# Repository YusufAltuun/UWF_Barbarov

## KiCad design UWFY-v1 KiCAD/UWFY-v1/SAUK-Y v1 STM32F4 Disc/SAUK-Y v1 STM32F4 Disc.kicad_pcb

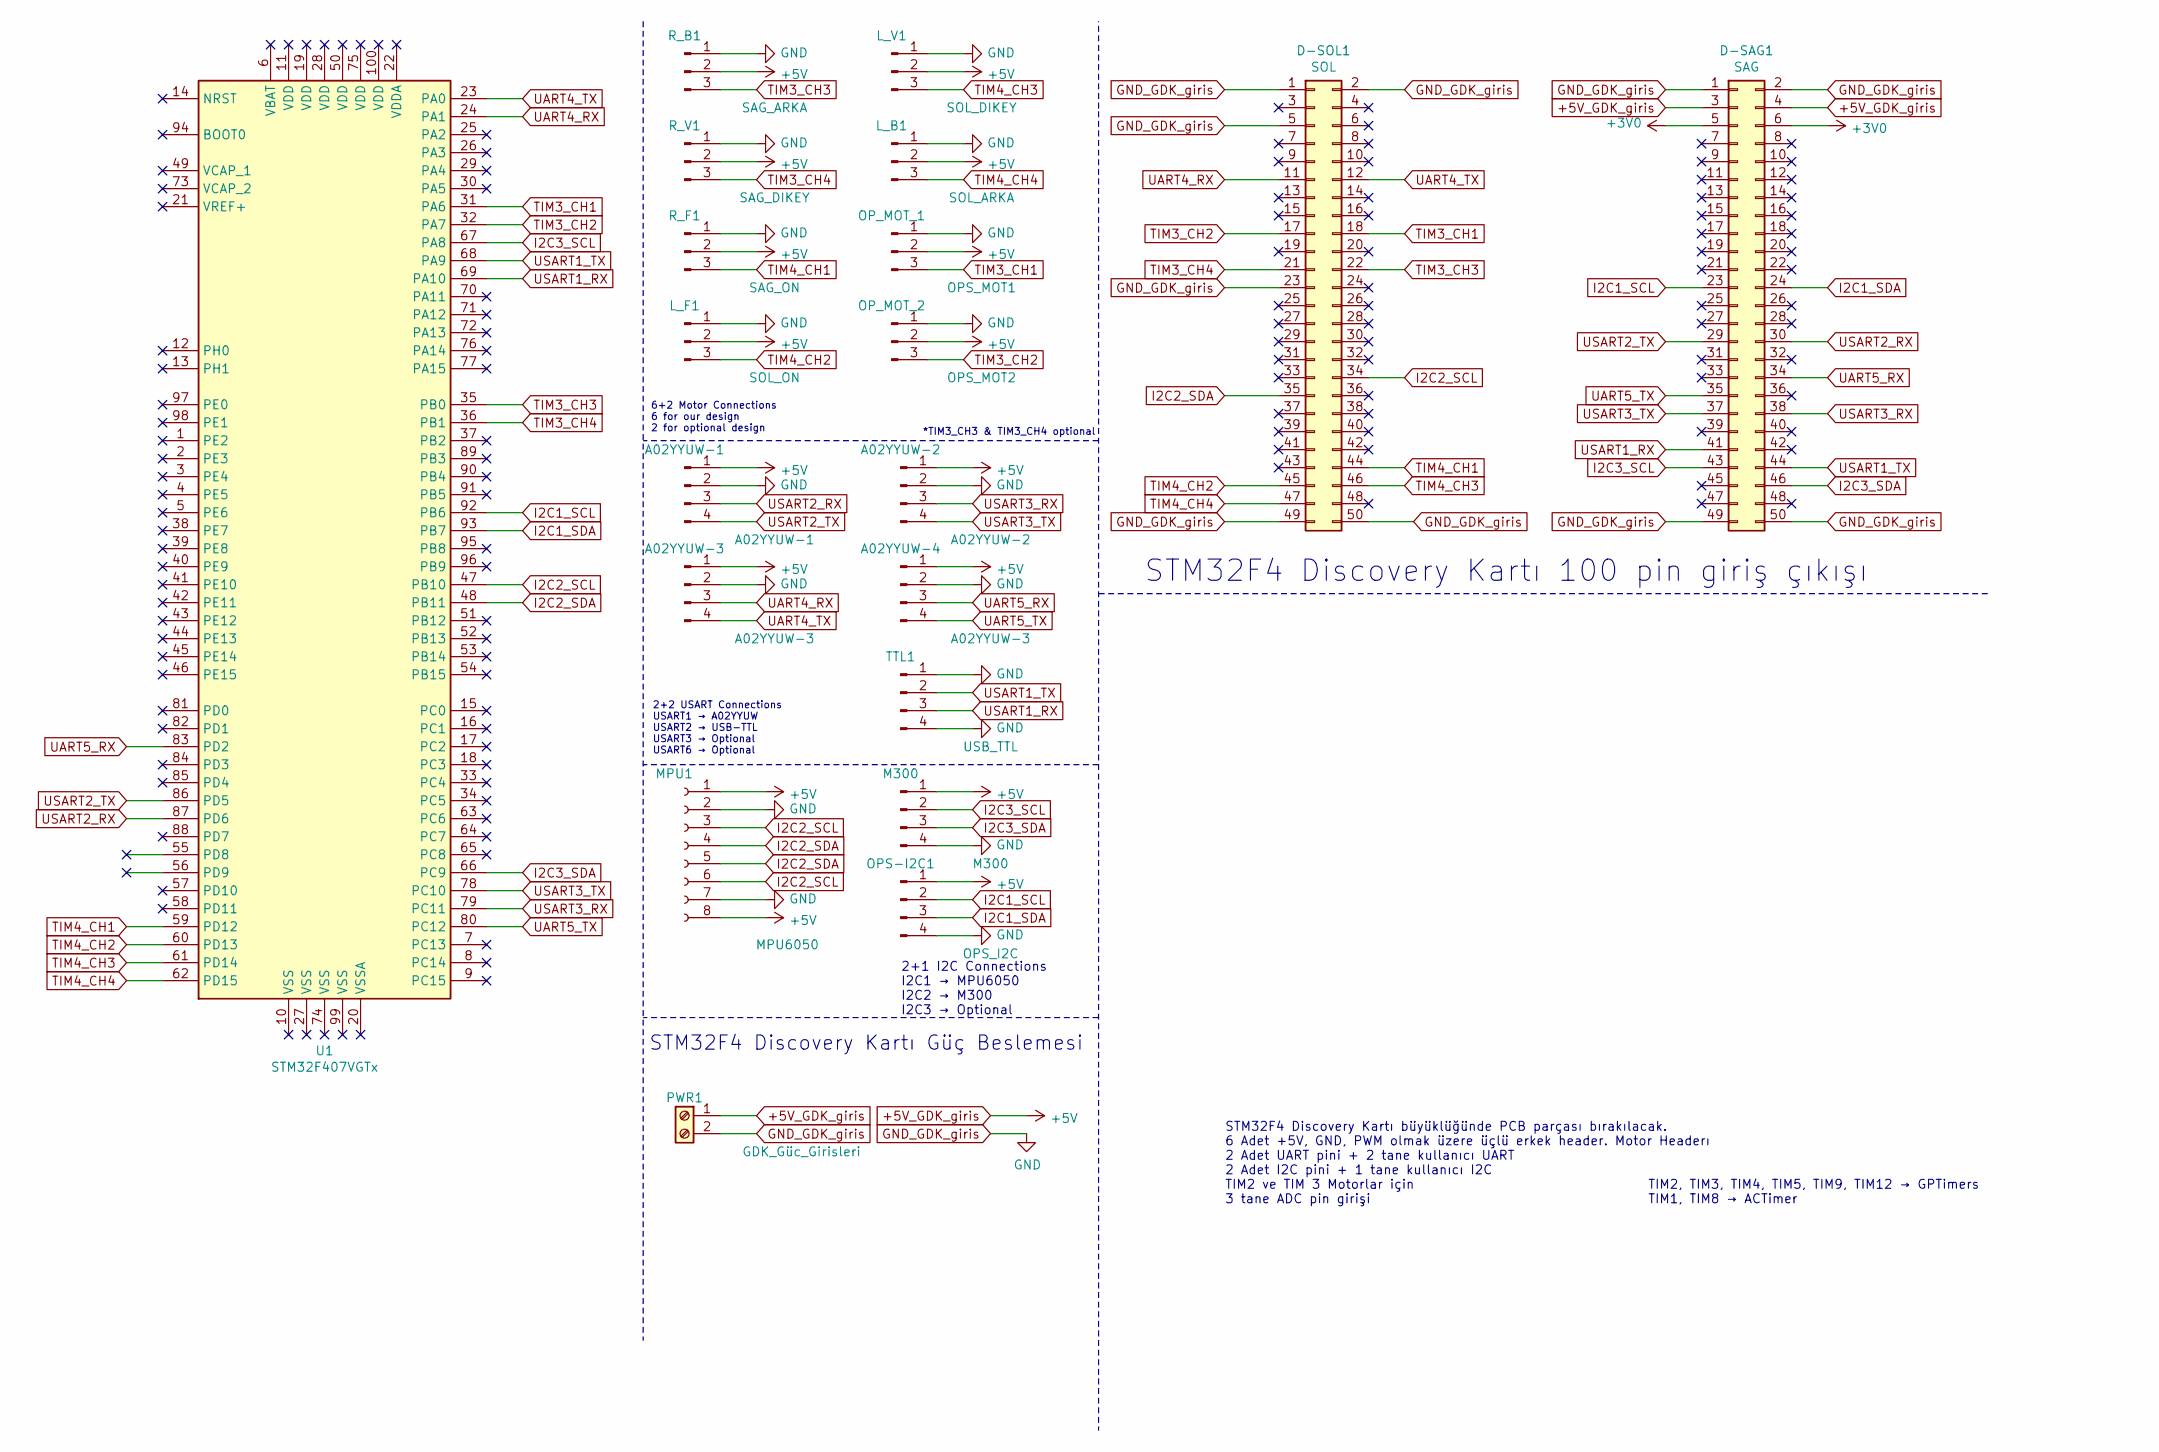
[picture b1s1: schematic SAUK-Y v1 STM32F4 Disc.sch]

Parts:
A02YYUW-1: A02YYUW-1; JST_EH_S4B-EH_1x04_P2.50mm_Horizontal
A02YYUW-2: A02YYUW-2; JST_EH_S4B-EH_1x04_P2.50mm_Horizontal
A02YYUW-3, A02YYUW-4: A02YYUW-3; JST_EH_S4B-EH_1x04_P2.50mm_Horizontal
D-SAG1: SAG; PinSocket_2x25_P2.54mm_Vertical
D-SOL1: SOL; PinSocket_2x25_P2.54mm_Vertical
L_B1: SOL_ARKA; JST_EH_S3B-EH_1x03_P2.50mm_Horizontal
L_F1: SOL_ON; JST_EH_S3B-EH_1x03_P2.50mm_Horizontal
L_V1: SOL_DIKEY; JST_EH_S3B-EH_1x03_P2.50mm_Horizontal
M300: M300; JST_EH_S4B-EH_1x04_P2.50mm_Horizontal
MPU1: MPU6050; PinSocket_1x08_P2.54mm_Horizontal
OPS-I2C1: OPS_I2C; JST_EH_B4B-EH-A_1x04_P2.50mm_Vertical
OP_MOT_1: OPS_MOT1; JST_EH_B3B-EH-A_1x03_P2.50mm_Vertical
OP_MOT_2: OPS_MOT2; JST_EH_B3B-EH-A_1x03_P2.50mm_Vertical
PWR1: GDK_Güc_Girisleri; TerminalBlock_MetzConnect_Type011_RT05502HBWC_1x02_P5.00mm_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
R_B1: SAG_ARKA; JST_EH_S3B-EH_1x03_P2.50mm_Horizontal
R_F1: SAG_ON; JST_EH_S3B-EH_1x03_P2.50mm_Horizontal
R_V1: SAG_DIKEY; JST_EH_S3B-EH_1x03_P2.50mm_Horizontal
TTL1: USB_TTL; PinSocket_1x04_P2.54mm_Vertical
U1: STM32F407VGTx; LQFP-100_14x14mm_P0.5mm

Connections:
+3V0: D-SAG1.5, D-SAG1.6
+5V_GDK_giris: A02YYUW-1.1, A02YYUW-2.1, A02YYUW-3.1, A02YYUW-4.1, D-SAG1.3, D-SAG1.4, L_B1.2, L_F1.2, L_V1.2, M300.1, MPU1.1, MPU1.8, OPS-I2C1.1, OP_MOT_1.2, OP_MOT_2.2, PWR1.1, R_B1.2, R_F1.2, R_V1.2
GND_GDK_giris: A02YYUW-1.2, A02YYUW-2.2, A02YYUW-3.2, A02YYUW-4.2, D-SAG1.1, D-SAG1.2, D-SAG1.49, D-SAG1.50, D-SOL1.1, D-SOL1.2, D-SOL1.5, D-SOL1.23, D-SOL1.49, D-SOL1.50, L_B1.1, L_F1.1, L_V1.1, M300.4, MPU1.2, MPU1.7, OPS-I2C1.4, OP_MOT_1.1, OP_MOT_2.1, PWR1.2, R_B1.1, R_F1.1, R_V1.1, TTL1.1, TTL1.4
I2C1_SCL: D-SAG1.23, OPS-I2C1.2, U1.92 (PB6)
I2C1_SDA: D-SAG1.24, OPS-I2C1.3, U1.93 (PB7)
I2C2_SCL: D-SOL1.34, MPU1.3, MPU1.6, U1.47 (PB10)
I2C2_SDA: D-SOL1.35, MPU1.4, MPU1.5, U1.48 (PB11)
I2C3_SCL: D-SAG1.43, M300.2, U1.67 (PA8)
I2C3_SDA: D-SAG1.46, M300.3, U1.66 (PC9)
TIM3_CH1: D-SOL1.18, OP_MOT_1.3, U1.31 (PA6)
TIM3_CH2: D-SOL1.17, OP_MOT_2.3, U1.32 (PA7)
TIM3_CH3: D-SOL1.22, R_B1.3, U1.35 (PB0)
TIM3_CH4: D-SOL1.21, R_V1.3, U1.36 (PB1)
TIM4_CH1: D-SOL1.44, R_F1.3, U1.59 (PD12)
TIM4_CH2: D-SOL1.45, L_F1.3, U1.60 (PD13)
TIM4_CH3: D-SOL1.46, L_V1.3, U1.61 (PD14)
TIM4_CH4: D-SOL1.47, L_B1.3, U1.62 (PD15)
UART4_RX: A02YYUW-3.3, D-SOL1.11, U1.24 (PA1)
UART4_TX: A02YYUW-3.4, D-SOL1.12, U1.23 (PA0)
UART5_RX: A02YYUW-4.3, D-SAG1.34, U1.83 (PD2)
UART5_TX: A02YYUW-4.4, D-SAG1.35, U1.80 (PC12)
USART1_RX: D-SAG1.41, TTL1.3, U1.69 (PA10)
USART1_TX: D-SAG1.44, TTL1.2, U1.68 (PA9)
USART2_RX: A02YYUW-1.3, D-SAG1.30, U1.87 (PD6)
USART2_TX: A02YYUW-1.4, D-SAG1.29, U1.86 (PD5)
USART3_RX: A02YYUW-2.3, D-SAG1.38, U1.79 (PC11)
USART3_TX: A02YYUW-2.4, D-SAG1.37, U1.78 (PC10)

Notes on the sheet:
STM32F4 Discovery Kartı büyüklüğünde PCB parçası bırakılacak. 6 Adet +5V, GND, PWM olmak üzere üçlü erkek header. Motor Headerı 2 Adet UART pini + 2 tane kullanıcı UART 2 Adet I2C pini + 1 tane kullanıcı I2C TIM2 ve TIM 3 Motorlar için 3 tane ADC pin girişi
TIM2, TIM3, TIM4, TIM5, TIM9, TIM12 → GPTimers TIM1, TIM8 → ACTimer
6+2 Motor Connections 6 for our design 2 for optional design
*TIM3_CH3 & TIM3_CH4 optional
2+2 USART Connections USART1 → A02YYUW USART2 → USB-TTL USART3 → Optional USART6 → Optional
2+1 I2C Connections I2C1 → MPU6050 I2C2 → M300 I2C3 → Optional
STM32F4 Discovery Kartı 100 pin giriş çıkışı
STM32F4 Discovery Kartı Güç Beslemesi

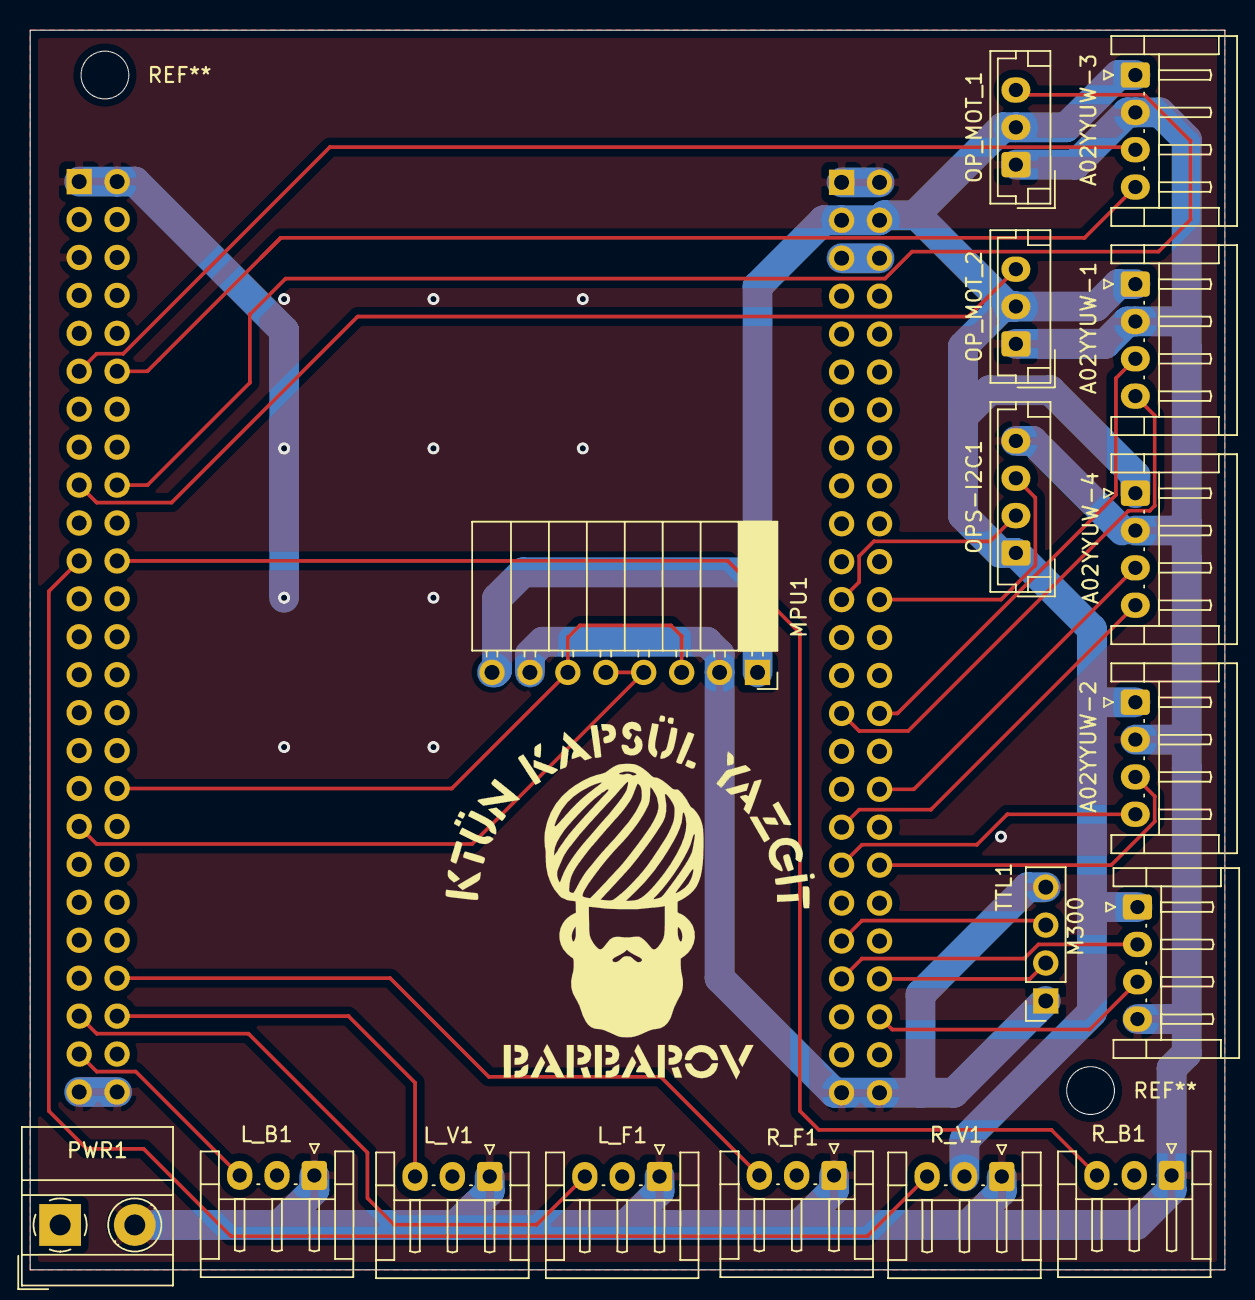
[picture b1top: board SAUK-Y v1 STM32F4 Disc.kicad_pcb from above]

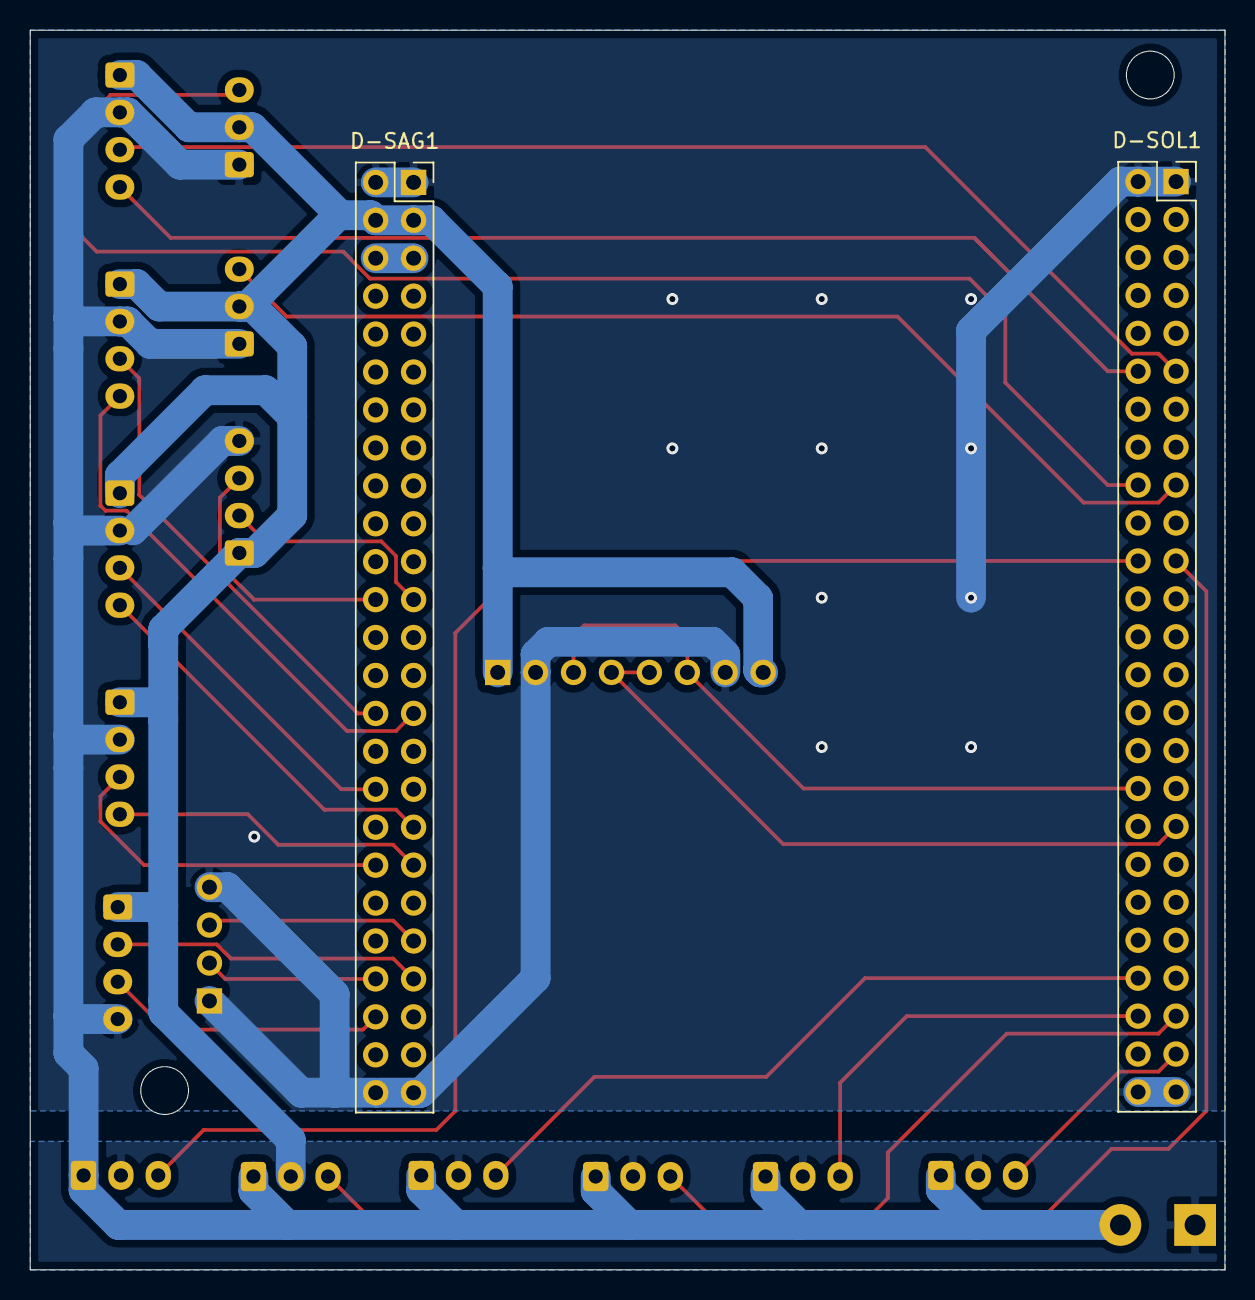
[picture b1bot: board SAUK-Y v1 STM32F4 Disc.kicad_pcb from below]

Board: 2 copper layers, 80.0 x 83.0 mm, 19 parts (2 on the bottom side), 27 nets.

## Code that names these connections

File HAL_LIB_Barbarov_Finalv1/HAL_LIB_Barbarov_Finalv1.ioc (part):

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Mcu.Name=STM32F407V(E-G)Tx
Mcu.Package=LQFP100
Mcu.UserName=STM32F407VGTx
PA0-WKUP.Mode=Asynchronous
PA0-WKUP.Signal=UART4_TX
PA1.Mode=Asynchronous
PA1.Signal=UART4_RX
PA10.Mode=Asynchronous
PA10.Signal=USART1_RX
PA6.Signal=S_TIM3_CH1
PA7.Signal=S_TIM3_CH2
PA8.Mode=I2C
PA8.Signal=I2C3_SCL
PA9.Mode=Asynchronous
PA9.Signal=USART1_TX
PB0.Signal=S_TIM3_CH3
PB1.Signal=S_TIM3_CH4
PB10.Mode=I2C
PB10.Signal=I2C2_SCL
PB11.Mode=I2C
PB11.Signal=I2C2_SDA
PB6.Mode=I2C
PB6.Signal=I2C1_SCL
PB7.Mode=I2C
PB7.Signal=I2C1_SDA
PC10.Mode=Asynchronous
PC10.Signal=USART3_TX
PC11.Mode=Asynchronous
PC11.Signal=USART3_RX
PC12.Mode=Asynchronous
PC12.Signal=UART5_TX
PC9.Mode=I2C
PC9.Signal=I2C3_SDA
PD12.Signal=S_TIM4_CH1
PD13.Signal=S_TIM4_CH2
PD14.Signal=S_TIM4_CH3
PD15.Signal=S_TIM4_CH4
PD2.Mode=Asynchronous
PD2.Signal=UART5_RX
PD5.Mode=Asynchronous
PD5.Signal=USART2_TX
PD6.Mode=Asynchronous
PD6.Signal=USART2_RX
RCC.HSE_VALUE=8000000
RCC.SYSCLKFreq_VALUE=168000000
RCC.SYSCLKSource=RCC_SYSCLKSOURCE_PLLCLK
board=STM32F407G-DISC1
boardIOC=true
